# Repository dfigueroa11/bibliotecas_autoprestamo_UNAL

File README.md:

# Autoprestamo de libros

Sistema de automatización de préstamo y devolución de Libros de las Bibliote dentro del campus de la Universidad Nacional de Colombia, incorporando la conexión entre puntos de prestamo y facilitando el proceso que a la fecha se implementa. El sistema tiene como objetivo principal reducir construir un sistema que pueda ser escalable y replicable de forma más economica.

Integrantes: 
* Maria Alejandra Salgado Herrera
* Emmanuel David Correa Morales
* Ferdy Eduardo Larrotta Ruiz
* Danny Esteban Portela Robayo
* Diego Alejandro Figueroa Del Castillo

## Organización del repositorio

### En la carpeta "[Sensibilizador_PCB](https://github.com/dfigueroa11/bibliotecas_autoprestamo_UNAL/tree/main/Sensibilizador_PCB)" se encuentran los diseños y esquemáticos llevados a cabo en el diseño del Sensibilizador del sistema.
### En la carpeta "[esquematico_ESP32](https://github.com/dfigueroa11/bibliotecas_autoprestamo_UNAL/tree/main/esquematico_ESP32)" se encuentran los diseños y esquemáticos llevados a cabo en el diseño del circuito logico y de control del sistema.
### "[Micropython](https://github.com/dfigueroa11/bibliotecas_autoprestamo_UNAL/tree/main/Micropython)" contiene los scripts utilizados para programar el microcontrolador de la solución.
### En "[Diseno_carcasa](https://github.com/dfigueroa11/bibliotecas_autoprestamo_UNAL/tree/main/Diseno_carcasa)" se encuentran los modelos 3D, planos, DXFs y consideraciones físicas para la carcasa. 
### "[Lista_materiales.xlsx](https://github.com/dfigueroa11/bibliotecas_autoprestamo_UNAL/blob/main/Lista_materiales.xlsx)" contiene la lista de materiales necesarios para el desarrollo del prototipo. 
### "[images](https://github.com/dfigueroa11/bibliotecas_autoprestamo_UNAL/tree/main/images)" almacena las imágenes utilizadas en la documentación y en los archivos readme de cada sección.

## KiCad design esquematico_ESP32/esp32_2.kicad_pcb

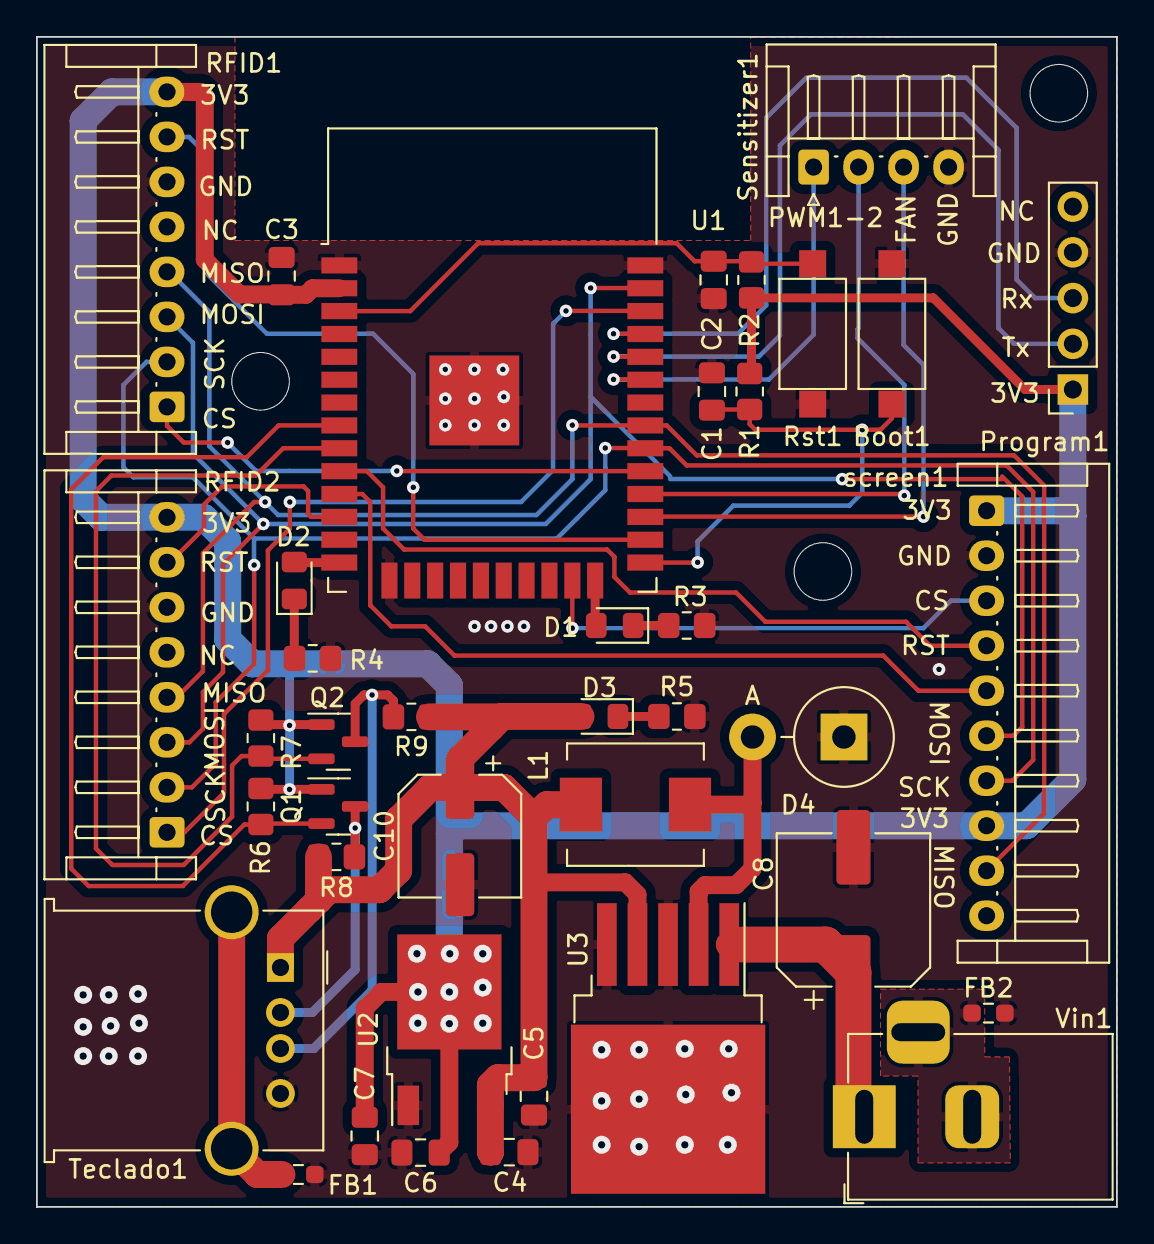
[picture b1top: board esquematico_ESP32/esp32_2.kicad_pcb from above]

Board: 2 copper layers, 60.0 x 65.0 mm, 42 parts (0 on the bottom side), 33 nets.

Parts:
Boot1: SW_Push; SW_SPST_CK_RS282G05A3
C1, C2: 1nf; C_0805_2012Metric_Pad1.18x1.45mm_HandSolder
C3: 100u; C_0805_2012Metric_Pad1.18x1.45mm_HandSolder
C4, C7: 100n; C_0805_2012Metric_Pad1.18x1.45mm_HandSolder
C5: 10u; C_0805_2012Metric_Pad1.18x1.45mm_HandSolder
C6: 22u; C_0805_2012Metric_Pad1.18x1.45mm_HandSolder
C8: 470u; CP_Elec_8x6.9
C10: 220u; CP_Elec_6.3x7.7
D1, D2, D3: LED; LED_0805_2012Metric_Pad1.15x1.40mm_HandSolder
D4: 1N5825; D_DO-201AE_P5.08mm_Vertical_AnodeUp
FB1, FB2: FerriteBead; R_0603_1608Metric_Pad0.98x0.95mm_HandSolder
L1: 68u; L_Neosid_SM-PIC0612H
Program1: Conn_01x05_Female; PinSocket_1x05_P2.54mm_Vertical
Q1, Q2: BSS138; SOT-23
R1, R2, R3, R4, R5, R6, R7, R8, R9: 10k; R_0805_2012Metric_Pad1.20x1.40mm_HandSolder
RFID1: J2; JST_EH_S8B-EH_1x08_P2.50mm_Horizontal
RFID2: J3; JST_EH_S8B-EH_1x08_P2.50mm_Horizontal
Rst1: Enable; SW_SPST_CK_RS282G05A3
Sensitizer1: Conn_01x04_Female; JST_EH_S4B-EH_1x04_P2.50mm_Horizontal
T1, T2, T3: MountingHole_3.2mm_M3_DIN965
Teclado1: USB_A; USB_A_Molex_67643_Horizontal
U1: ESP32-WROOM-32
U2: LM1117-3.3; TO-252-2
U3: LM2596S-5; TO-263-5_TabPin3
Vin1: Jack-DC; BarrelJack_Horizontal
screen1: J5; JST_EH_S10B-EH_1x10_P2.50mm_Horizontal

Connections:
+3V3: C3.1, C6.1, C7.1, Program1.1, Q1.1 (G), Q2.1 (G), R1.1, R2.1, R6.1, R7.1, RFID1.8, RFID2.8, U1.2 (VDD), U2.2 (VO), screen1.1, screen1.8
+5V: C4.1, C5.1, C10.1, D3.2 (A), L1.2, R8.1, R9.1, Teclado1.1 (VBUS), U2.3 (VI), U3.4 (FB)
+12V: C8.1, U3.1 (VIN), Vin1.1
/CLC_KEYBOARD: Q1.2 (S), R6.2, U1.8 (IO32)
/CONEX: D2.2 (A), U1.14 (IO12)
/CS_Display: U1.23 (IO15), screen1.3
/CS_LECTOR_1: RFID1.1, U1.29 (IO5)
/CS_LECTOR_2: RFID2.1, U1.36 (IO22)
/DATA_KEYBOARD: Q2.2 (S), R7.2, U1.9 (IO33)
/D/C: U1.11 (IO26), screen1.5
/EN: C2.2, R2.2, Rst1.2, U1.3 (EN)
/INFO: D1.2 (A), U1.24 (IO2)
/IOD: Boot1.2, C1.2, R1.2, U1.25 (IO0)
/MAGNE_1: Sensitizer1.2, U1.28 (IO17)
/MAGNE_2: Sensitizer1.1, U1.33 (IO21)
/MAGNE_3: Sensitizer1.3, U1.27 (IO16)
/MISO: RFID1.4, RFID2.4, U1.31 (IO19), screen1.9
/MOSI: RFID1.3, RFID2.3, U1.37 (IO23), screen1.6
/RST_1: RFID1.7, U1.26 (IO4)
/RST_2: RFID2.7, U1.12 (IO27)
/RST_D: U1.10 (IO25), screen1.4
/SCK: RFID1.2, RFID2.2, U1.30 (IO18), screen1.7
/perifericos/Data_5v_keyboard: Q1.3 (D), R8.2, Teclado1.2 (D-)
/perifericos/clk_5V_keyboard: Q2.3 (D), R9.2, Teclado1.3 (D+)
GND: Boot1.1, C1.1, C2.1, C3.2, C4.2, C5.2, C6.2, C7.2, C8.2, C10.2, D4.1 (K), FB1.2, FB2.1, Program1.4, R3.2, R4.2, R5.2, RFID1.6, RFID2.6, Rst1.1, Sensitizer1.4, Teclado1.4 (GND), U1.1 (GND), U1.15 (GND), U1.38 (GND), U1.39 (GND), U2.1 (GND), U3.3 (GND), U3.5 (~ON/OFF), screen1.2
unnamed: D1.1 (K), R3.1
unnamed: D2.1 (K), R4.1
unnamed: D3.1 (K), R5.1
unnamed: D4.2 (A), L1.1, U3.2 (OUT)
unnamed: FB1.1, Teclado1.5 (Shield)
unnamed: FB2.2, Vin1.2, Vin1.3
unnamed: Program1.2, U1.34 (RXD0/IO3)
unnamed: Program1.3, U1.35 (TXD0/IO1)

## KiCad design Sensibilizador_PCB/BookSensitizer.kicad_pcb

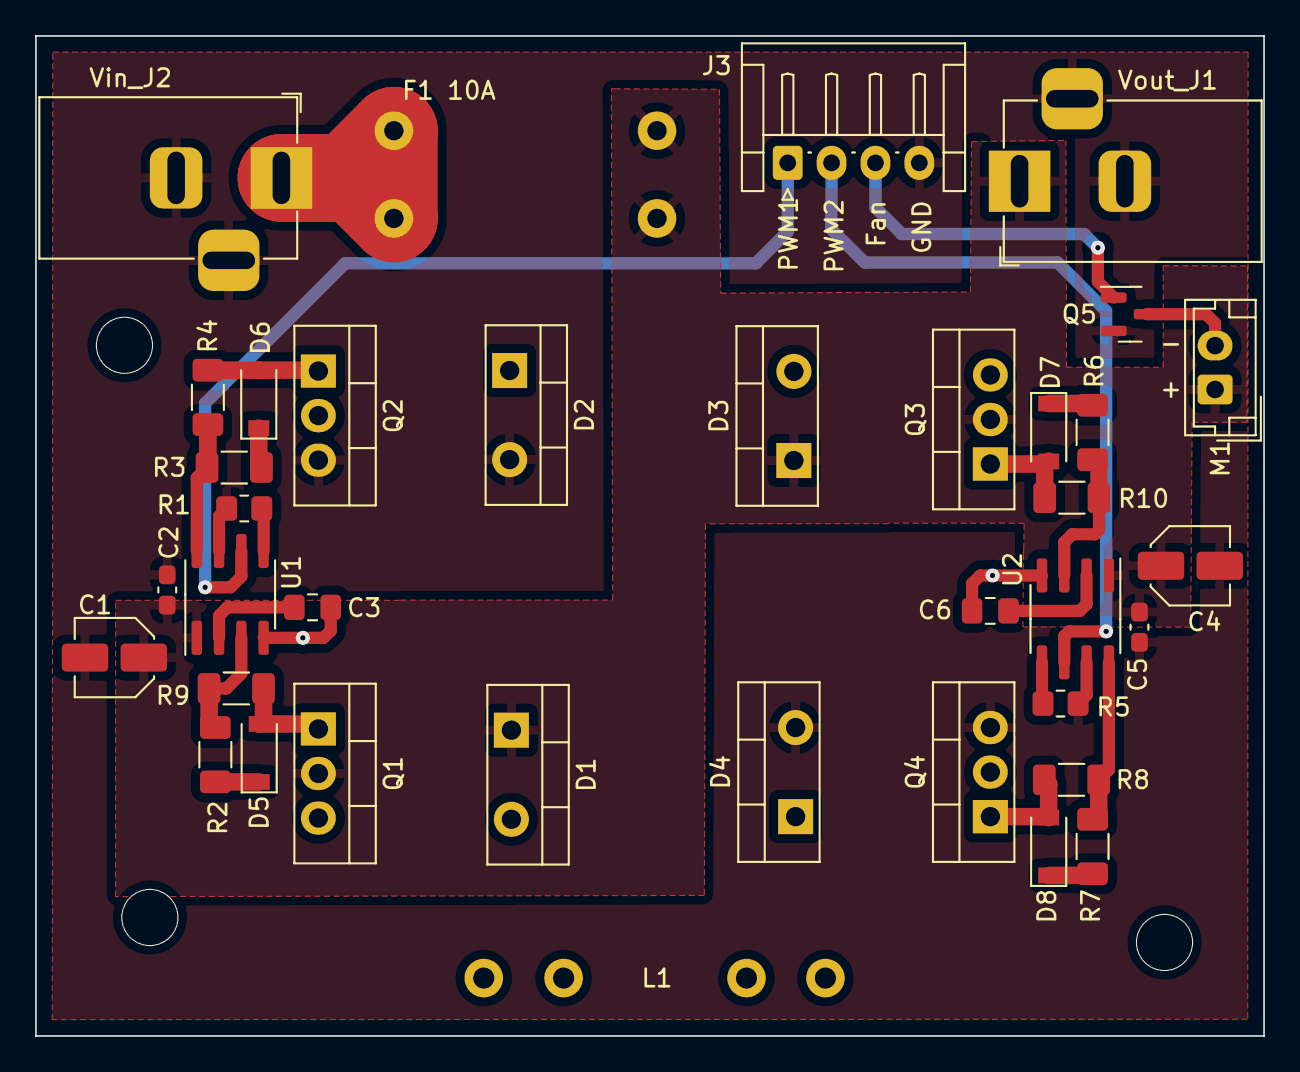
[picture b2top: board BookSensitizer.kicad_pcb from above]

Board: 2 copper layers, 70.0 x 57.0 mm, 40 parts (0 on the bottom side), 25 nets.

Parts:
C1, C4: 1uF 50V; C_Elec_4x5.4
C2, C5: 100nF 50V; C_0603_1608Metric_Pad1.08x0.95mm_HandSolder
C3, C6: 10nF 25V; C_0805_2012Metric_Pad1.18x1.45mm_HandSolder
D1, D2, D3, D4: F10L60u; TO-220-2_Vertical
D5, D6, D7, D8: SS34FA; D_SOD-123
F1 10A: Fuse; porta_fusible
J3: Conn_inputs; JST_EH_S4B-EH_1x04_P2.50mm_Horizontal
L1: L; conector Faston
M1: Fan; JST_EH_B2B-EH-A_1x02_P2.50mm_Vertical
Q1, Q2, Q3, Q4: IRF630; TO-220-3_Vertical
Q5: SI2302; SOT-23
R1, R5: R; R_0805_2012Metric_Pad1.20x1.40mm_HandSolder
R2, R3, R4, R6, R7, R8, R9, R10: 2.74 1/4W; R_1206_3216Metric_Pad1.30x1.75mm_HandSolder
T1, T2, T3: MountingHole_3.2mm_M3
U1, U2: LM5104M; SOIC-8_3.9x4.9mm_P1.27mm
Vin_J2: Jack_in; BarrelJack_Horizontal
Vout_J1: Jack_out; BarrelJack_Horizontal

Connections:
+12V: C1.1, C2.1, C4.1, C5.1, D1.1 (K), D3.1 (K), F1 10A.2, M1.1 (+), Q1.2 (D), Q3.2 (D), U1.1 (VDD), U2.1 (VDD), Vout_J1.1
/driver1/G_High: D5.2 (A), Q1.1 (G), R9.2
/driver1/G_low: D6.2 (A), Q2.1 (G), R4.2
/driver1/Hs: C3.2, D1.2 (A), D2.1 (K), L1.1, Q1.3 (S), Q2.2 (D), U1.4 (HS)
/driver2/G_High: D7.2 (A), Q3.1 (G), R10.2
/driver2/G_low: D8.2 (A), Q4.1 (G), R8.2
/driver2/Hs: C6.2, D3.2 (A), D4.1 (K), L1.2, Q3.3 (S), Q4.2 (D), U2.4 (HS)
/in_1: J3.1, U1.6 (LI)
/in_2: J3.2, U2.6 (LI)
/in_3: J3.3, Q5.1 (G)
GND: C1.2, C2.2, C4.2, C5.2, D2.2 (A), D4.2 (A), J3.4, Q2.3 (S), Q4.3 (S), Q5.2 (S), R1.2, R5.2, U1.7 (VSS), U2.7 (VSS), Vin_J2.2, Vout_J1.2
unnamed: C3.1, U1.2 (HB)
unnamed: C6.1, U2.2 (HB)
unnamed: D5.1 (K), R2.2
unnamed: D6.1 (K), R3.2
unnamed: D7.1 (K), R6.2
unnamed: D8.1 (K), R7.2
unnamed: F1 10A.1, Vin_J2.1
unnamed: M1.2 (-), Q5.3 (D)
unnamed: R1.1, U1.5 (RT)
unnamed: R2.1, R9.1, U1.3 (HO)
unnamed: R3.1, R4.1, U1.8 (LO)
unnamed: R5.1, U2.5 (RT)
unnamed: R6.1, R10.1, U2.3 (HO)
unnamed: R7.1, R8.1, U2.8 (LO)

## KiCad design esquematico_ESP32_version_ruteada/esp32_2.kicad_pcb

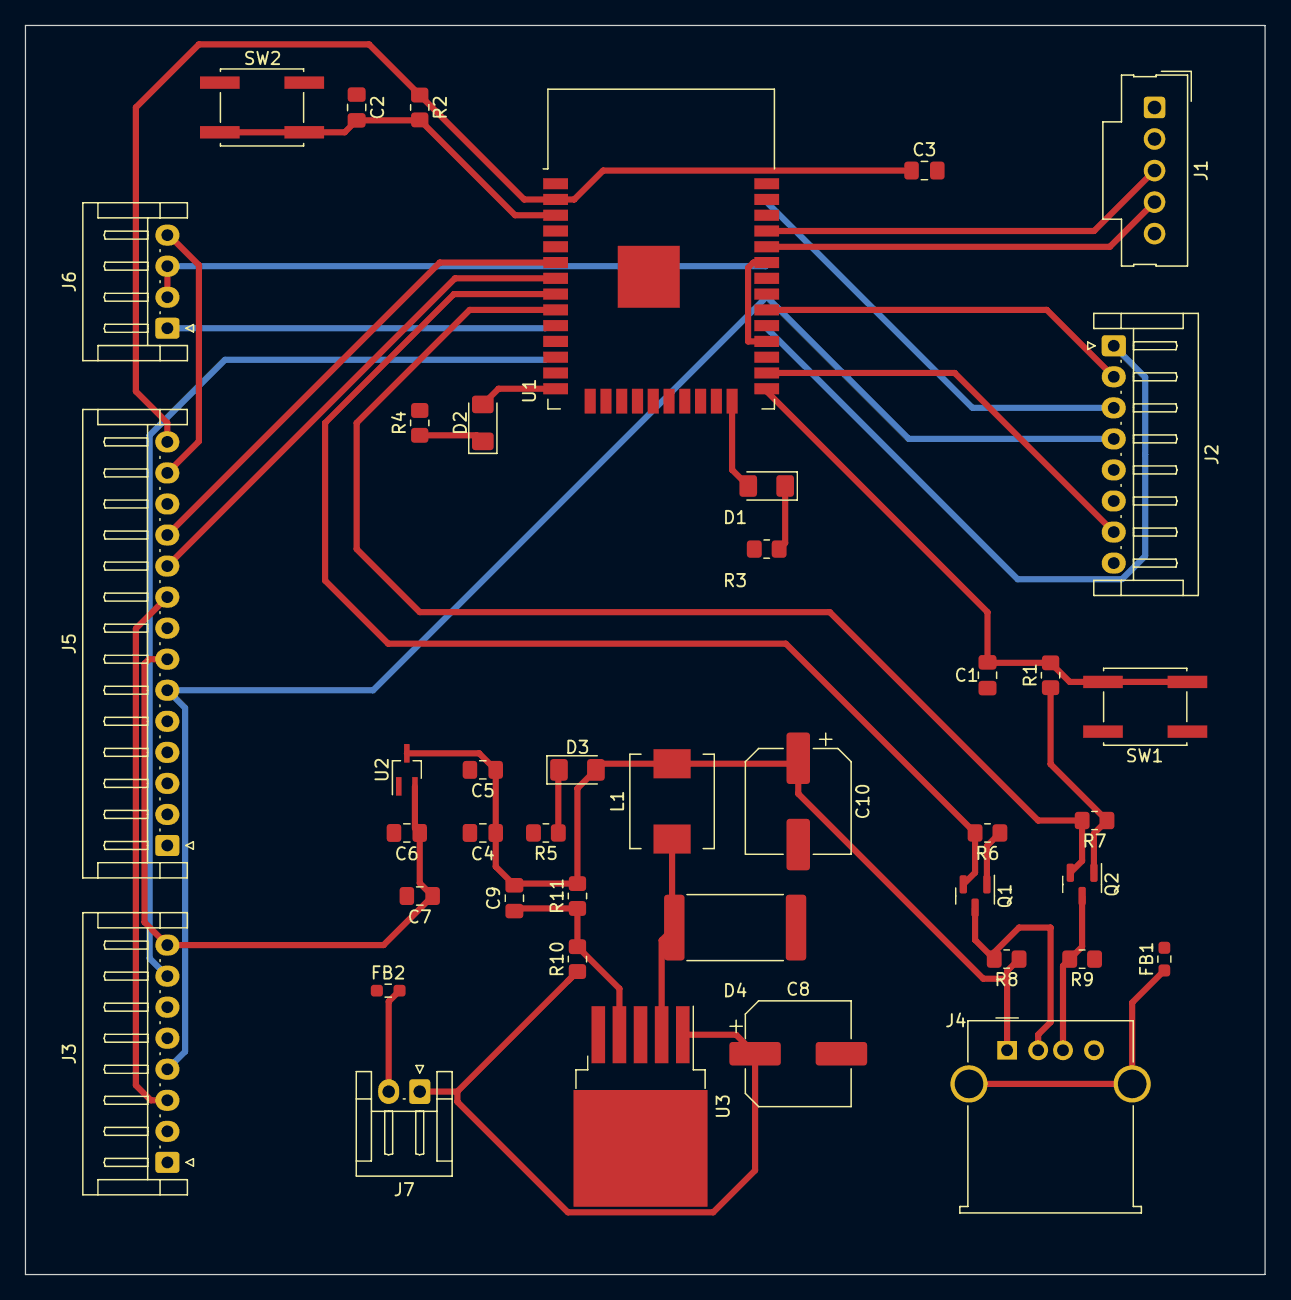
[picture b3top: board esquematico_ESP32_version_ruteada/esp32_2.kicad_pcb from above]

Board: 2 copper layers, 99.8 x 100.6 mm, 42 parts (0 on the bottom side), 33 nets.

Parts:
C1, C2, C4, C5, C6, C7, C9: C; C_0805_2012Metric_Pad1.18x1.45mm_HandSolder
C3: C_Polarized; C_0805_2012Metric_Pad1.18x1.45mm_HandSolder
C8, C10: C_Polarized; CP_Elec_8x6.9
D1, D2, D3: LED; LED_1206_3216Metric_Pad1.42x1.75mm_HandSolder
D4: DIODE; R_4020_10251Metric_Pad1.65x5.30mm_HandSolder
FB1, FB2: FerriteBead; R_0603_1608Metric_Pad0.98x0.95mm_HandSolder
J1: Conn_01x05_Female; Molex_SL_171971-0005_1x05_P2.54mm_Vertical
J2, J3: Conn_01x08_Female; JST_EH_S8B-EH_1x08_P2.50mm_Horizontal
J4: USB_A; USB_A_Molex_67643_Horizontal
J5: Conn_01x14_Female; JST_EH_S14B-EH_1x14_P2.50mm_Horizontal
J6: Conn_01x04_Female; JST_EH_S4B-EH_1x04_P2.50mm_Horizontal
J7: Conn_01x02_Female; JST_EH_S2B-EH_1x02_P2.50mm_Horizontal
L1: L; L_Neosid_SM-PIC0612H
Q1, Q2: BSS138; SOT-23
R1, R2, R3, R4, R5, R6, R7, R8, R9, R10, R11: R; R_0805_2012Metric_Pad1.20x1.40mm_HandSolder
SW1, SW2: SW_Push; SW_SPST_EVQQ2
U1: ESP32-WROOM-32
U2: LM1117-3.3; SOT-323_SC-70_Handsoldering
U3: LM2596S-5; TO-263-5_TabPin3

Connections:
+3V3: C3.1, C6.1, C7.1, J2.8, J3.8, J5.7, J5.14, Q1.1 (G), Q2.1 (G), R1.1, R2.1, R6.1, R7.1, U1.2 (VDD), U2.2 (VO)
+5V: C4.1, C5.1, C9.2, C10.1, D3.2 (A), J1.1, J4.1 (VBUS), L1.2, R8.1, R9.1, R11.2, U2.3 (VI)
+12V: C8.1, J7.1, R10.1, U3.1 (VIN)
/CLC_KEYBOARD: Q1.2 (S), R6.2, U1.8 (IO32)
/CONEX: D2.2 (A), U1.14 (IO12)
/CS_Display: J5.12, U1.23 (IO15)
/CS_LECTOR_2: J3.1, U1.36 (IO22)
/CS_lector_1: J2.1, U1.29 (IO5)
/DATA_KEYBOARD: Q2.2 (S), R7.2, U1.9 (IO33)
/D/C: J5.10, U1.7 (IO35)
/EN: C2.2, R2.2, SW2.2, U1.3 (EN)
/INFO: D1.2 (A), U1.24 (IO2)
/IOD: C1.2, R1.2, SW1.2, U1.25 (IO0)
/MAGNE_2: J6.2, J6.3, U1.28 (IO17), U1.33 (IO21)
/MAGNE_3: J6.1, U1.10 (IO25)
/MISO: J2.4, J3.4, J5.6, U1.31 (IO19)
/MOSI: J2.3, J3.3, J5.9, U1.37 (IO23)
/RST_2: J3.7, U1.12 (IO27)
/RST_D: J5.11, U1.6 (IO34)
/Rst_1: J2.7, U1.26 (IO4)
/SCK: J2.2, J3.2, J5.8, U1.30 (IO18)
/perifericos/Data_5v_keyboard: J4.2 (D-), Q1.3 (D), R8.2
/perifericos/clk_5V_keyboard: J4.3 (D+), Q2.3 (D), R9.2
GND: C1.1, C2.1, C3.2, C4.2, C5.2, C6.2, C7.2, C8.2, C10.2, D4.1 (K), FB1.2, FB2.1, J1.2, J2.6, J3.6, J4.4 (GND), J5.13, J6.4, R3.2, R4.2, R5.2, SW1.1, SW2.1, U1.1 (GND), U1.15 (GND), U1.38 (GND), U1.39 (GND), U2.1 (GND), U3.3 (GND), U3.5 (~ON/OFF)
unnamed: C9.1, R10.2, R11.1, U3.4 (FB)
unnamed: D1.1 (K), R3.1
unnamed: D2.1 (K), R4.1
unnamed: D3.1 (K), R5.1
unnamed: D4.2 (A), L1.1, U3.2 (OUT)
unnamed: FB1.1, J4.5 (Shield)
unnamed: FB2.2, J7.2
unnamed: J1.3, U1.35 (TXD0/IO1)
unnamed: J1.4, U1.34 (RXD0/IO3)

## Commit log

2022-05-10 PCB para el sensibilizador
    Se añade archivos de Kicad para la PCB del sensibilizador, así como librerías para el driver LM5104M
2022-05-10 Corrección
2022-05-10 pequeño cambio
2022-05-10 Sensibilizador con valores
    Se agregaron valores a los elementos de los drivers y se modificó la topología.
2022-05-10 check list del diseño driver puente H
2022-05-12 huellas agregadas
2022-05-12 Rectificador primera versión
2022-05-16 Listo pa tirar lineas
2022-05-16 Organizado 0 aire
    0 aire
    ready pa rutear
2022-05-16 mini cambio en label de RHon
2022-05-16 la mitad de los trazos
2022-05-16 PCB lista
2022-05-16 Con tornillos
2022-05-16 FinalComprobada
2022-05-17 mini arreglo para conectar una tierra
2022-05-17 Version ruteada
2022-05-17 borrarndo todo
2022-05-17 listo para rutear la ESP
2022-05-18 prueba de cambios
2022-05-18 ruteo listo con un posible error en footprint esp32
2022-05-18 correción de un pulsador
2022-05-18 se agregaron los valores (pendiente última revisión)
2022-05-19 diseño listo
2022-05-20 Correciones de la clase
2022-05-20 huecos listos
2022-05-20 Alternativa_Acomodada
2022-05-20 placa terminada
2022-05-20 Gerber Generados
2022-05-21 ajuste final
2022-05-21 Enviado
2022-05-21 placas terminadas
2022-06-02 boom creado
2022-06-03 lista de materiales
2022-06-03 Lista de compras
2022-06-03 Actualización lista de materiales
2022-06-05 compras bogotá
2022-06-07 Carcasa
2022-06-10 ValoresCorregidos
    Algunos valores de resistencias fueron corregidos y coinciden con la placa.
    Valores de resistencias en los leds.
2022-06-10 arreglos carcasa
2022-06-17 Carcasa final
2022-06-19 Archivos de simulación bobina
2022-06-20 Diseño bobina Hemholtz
2022-06-30 pruebas
2022-07-01 EsquematicoLTspice
2022-07-01 simulación desmagnetizador
2022-07-02 actualizacion de eclado
2022-07-02 imagenes.raw actualizadas
2022-07-02 actualizar imagenes
2022-07-02 MQTT variables
2022-07-03 emmanuel
2022-07-03 Union
2022-07-03 desmagnetizador simulations
2022-07-03 cambios_02
2022-07-03 integracion1.0
2022-07-04 comprobacion de contraseña
2022-07-04 logica_lista
2022-07-04 bibliotecas_main_funciones
2022-07-04 simulaciones desmagnetizador
2022-07-04 actualizar
2022-07-04 video desmagnetizador
2022-07-05 Simulacion Magnetizador Terminada
2022-07-05 video funcionamiento conjunto
